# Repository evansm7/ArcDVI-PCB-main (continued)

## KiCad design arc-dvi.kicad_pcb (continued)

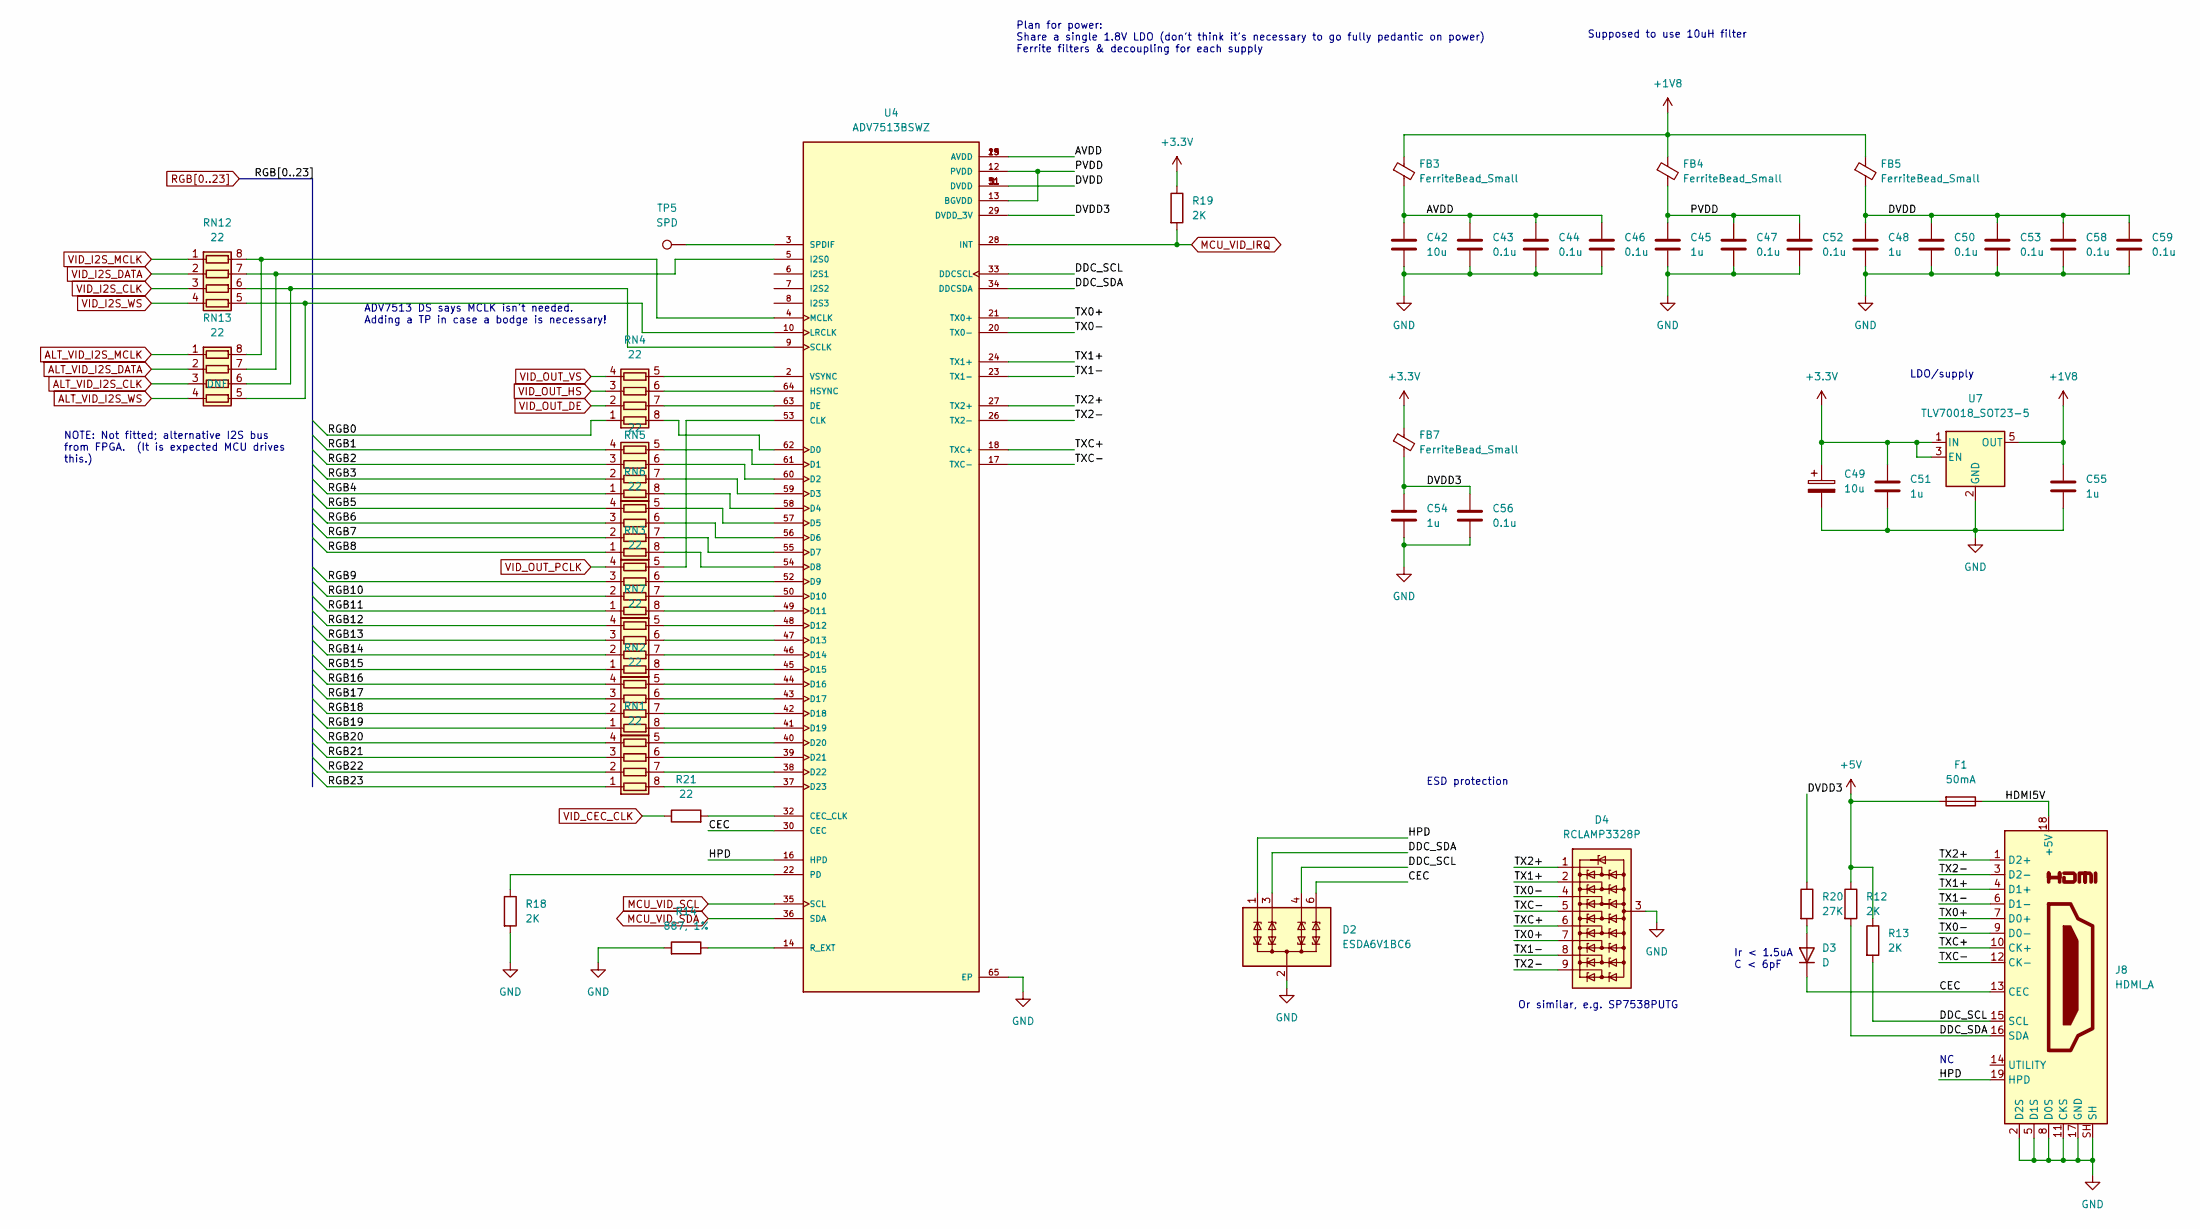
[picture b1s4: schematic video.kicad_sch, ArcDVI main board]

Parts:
C42: 10u; C_0603_1608Metric
C43, C44, C46, C47, C50, C52, C53, C56, C58, C59: 0.1u; C_0603_1608Metric
C45, C48, C51, C54, C55: 1u; C_0603_1608Metric
C49: 10u; CP_EIA-3528-21_Kemet-B
D2: ESDA6V1BC6; SOT-23-6
D3: D; D_0603_1608Metric
D4: RCLAMP3328P; UDFN-9_1.0x3.8mm_P0.5mm
F1: 50mA; Fuse_1206_3216Metric_Pad1.42x1.75mm_HandSolder
FB3, FB4, FB5, FB7: FerriteBead_Small; L_0603_1608Metric
J8: HDMI_A; HDMI_A_Molex_208658-1001_Horizontal
R12, R13, R18, R19: 2K; R_0603_1608Metric
R14: 887, 1%; R_0603_1608Metric
R20: 27K; R_0603_1608Metric
R21: 22; R_0603_1608Metric
RN1, RN2, RN3, RN4, RN5, RN6, RN7, RN12, RN13: 22; R_Array_Convex_4x0603
TP5: SPD; TestPoint_Pad_D1.0mm
U4: ADV7513BSWZ; QFP50P1200X1200X160-65N; PARTREV B
U7: TLV70018_SOT23-5; SOT-23-5

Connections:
+1V8: C55.1, FB3.1, FB4.1, FB5.1, U7.5 (OUT); also elsewhere on the board
+3V3: C49.1, C51.1, FB7.1, R19.1, U7.1 (IN), U7.3 (EN); also elsewhere on the board
+5V: F1.2, R12.1, R13.1; also elsewhere on the board
/Video/AVDD: C42.1, C43.1, C44.1, C46.1, FB3.2, U4.15 (AVDD), U4.19 (AVDD), U4.25 (AVDD)
/Video/CEC: D2.6 (TVS4), D3.1 (K), J8.13 (CEC), U4.30 (CEC)
/Video/DDC_SCL: D2.4 (TVS3), J8.15 (SCL), R13.2, U4.33 (DDCSCL)
/Video/DDC_SDA: D2.3 (TVS2), J8.16 (SDA), R12.2, U4.34 (DDCSDA)
/Video/DVDD: C48.1, C50.1, C53.1, C58.1, C59.1, FB5.2, U4.1 (DVDD), U4.11 (DVDD), U4.31 (DVDD), U4.51 (DVDD)
/Video/DVDD3: C54.1, C56.1, FB7.2, R20.1, U4.29 (DVDD_3V)
/Video/HDMI5V: F1.1, J8.18 (+5V)
/Video/HPD: D2.1 (TVS1), J8.19 (HPD), U4.16 (HPD)
/Video/PVDD: C45.1, C47.1, C52.1, FB4.2, U4.12 (PVDD), U4.13 (BGVDD)
/Video/TX0+: D4.7 (K6), J8.7 (D0+), U4.21 (TX0+)
/Video/TX0-: D4.4 (K3), J8.9 (D0-), U4.20 (TX0−)
/Video/TX1+: D4.2 (K2), J8.4 (D1+), U4.24 (TX1+)
/Video/TX1-: D4.8 (K7), J8.6 (D1-), U4.23 (TX1−)
/Video/TX2+: D4.1 (K1), J8.1 (D2+), U4.27 (TX2+)
/Video/TX2-: D4.9 (K8), J8.3 (D2-), U4.26 (TX2−)
/Video/TXC+: D4.6 (K5), J8.10 (CK+), U4.18 (TXC+)
/Video/TXC-: D4.5 (K4), J8.12 (CK-), U4.17 (TXC−)
ALT_VID_I2S_CLK: RN13.3 (R3.1); also elsewhere on the board
ALT_VID_I2S_DATA: RN13.2 (R2.1); also elsewhere on the board
ALT_VID_I2S_MCLK: RN13.1 (R1.1); also elsewhere on the board
ALT_VID_I2S_WS: RN13.4 (R4.1); also elsewhere on the board
GND: C42.2, C43.2, C44.2, C45.2, C46.2, C47.2, C48.2, C49.2, C50.2, C51.2, C52.2, C53.2, C54.2, C55.2, C56.2, C58.2, C59.2, D2.2 (COM), D2.5 (COM), D4.3 (A), J8.2 (D2S), J8.5 (D1S), J8.8 (D0S), J8.11 (CKS), J8.17 (GND), J8.SH, R14.2, R18.2, U4.65 (EP), U7.2 (GND); also elsewhere on the board
MCU_VID_IRQ: R19.2, U4.28 (INT); also elsewhere on the board
MCU_VID_SCL: U4.35 (SCL); also elsewhere on the board
MCU_VID_SDA: U4.36 (SDA); also elsewhere on the board
unnamed: D3.2 (A), R20.2
unnamed: R14.1, U4.14 (R_EXT)
unnamed: R18.1, U4.22 (PD)
unnamed: R21.2, U4.32 (CEC_CLK)
unnamed: RN1.5 (R4.2), U4.40 (D20)
unnamed: RN1.6 (R3.2), U4.39 (D21)
unnamed: RN1.7 (R2.2), U4.38 (D22)
unnamed: RN1.8 (R1.2), U4.37 (D23)
unnamed: RN2.5 (R4.2), U4.44 (D16)
unnamed: RN2.6 (R3.2), U4.43 (D17)
unnamed: RN2.7 (R2.2), U4.42 (D18)
unnamed: RN2.8 (R1.2), U4.41 (D19)
unnamed: RN3.5 (R4.2), U4.53 (CLK)
unnamed: RN3.6 (R3.2), U4.52 (D9)
unnamed: RN3.7 (R2.2), U4.50 (D10)
unnamed: RN3.8 (R1.2), U4.49 (D11)
unnamed: RN4.5 (R4.2), U4.2 (VSYNC)
unnamed: RN4.6 (R3.2), U4.64 (HSYNC)
unnamed: RN4.7 (R2.2), U4.63 (DE)
unnamed: RN4.8 (R1.2), U4.62 (D0)
unnamed: RN5.5 (R4.2), U4.61 (D1)
unnamed: RN5.6 (R3.2), U4.60 (D2)
unnamed: RN5.7 (R2.2), U4.59 (D3)
unnamed: RN5.8 (R1.2), U4.58 (D4)
unnamed: RN6.5 (R4.2), U4.57 (D5)
unnamed: RN6.6 (R3.2), U4.56 (D6)
unnamed: RN6.7 (R2.2), U4.55 (D7)
unnamed: RN6.8 (R1.2), U4.54 (D8)
unnamed: RN7.5 (R4.2), U4.48 (D12)
unnamed: RN7.6 (R3.2), U4.47 (D13)
unnamed: RN7.7 (R2.2), U4.46 (D14)
unnamed: RN7.8 (R1.2), U4.45 (D15)
unnamed: RN12.5 (R4.2), RN13.5 (R4.2), U4.10 (LRCLK)
unnamed: RN12.6 (R3.2), RN13.6 (R3.2), U4.9 (SCLK)
unnamed: RN12.7 (R2.2), RN13.7 (R2.2), U4.5 (I2S0)
unnamed: RN12.8 (R1.2), RN13.8 (R1.2), U4.4 (MCLK)
unnamed: TP5.1, U4.3 (SPDIF)
RGB0: RN4.1 (R1.1); also elsewhere on the board
RGB1: RN5.4 (R4.1); also elsewhere on the board
RGB2: RN5.3 (R3.1); also elsewhere on the board
RGB3: RN5.2 (R2.1); also elsewhere on the board
RGB4: RN5.1 (R1.1); also elsewhere on the board
RGB5: RN6.4 (R4.1); also elsewhere on the board
RGB6: RN6.3 (R3.1); also elsewhere on the board
RGB7: RN6.2 (R2.1); also elsewhere on the board
RGB8: RN6.1 (R1.1); also elsewhere on the board
RGB9: RN3.3 (R3.1); also elsewhere on the board
RGB10: RN3.2 (R2.1); also elsewhere on the board
RGB11: RN3.1 (R1.1); also elsewhere on the board
RGB12: RN7.4 (R4.1); also elsewhere on the board
RGB13: RN7.3 (R3.1); also elsewhere on the board
RGB14: RN7.2 (R2.1); also elsewhere on the board
RGB15: RN7.1 (R1.1); also elsewhere on the board
RGB16: RN2.4 (R4.1); also elsewhere on the board
RGB17: RN2.3 (R3.1); also elsewhere on the board
RGB18: RN2.2 (R2.1); also elsewhere on the board
RGB19: RN2.1 (R1.1); also elsewhere on the board
RGB20: RN1.4 (R4.1); also elsewhere on the board
RGB21: RN1.3 (R3.1); also elsewhere on the board
RGB22: RN1.2 (R2.1); also elsewhere on the board
RGB23: RN1.1 (R1.1); also elsewhere on the board
VID_CEC_CLK: R21.1; also elsewhere on the board
VID_I2S_CLK: RN12.3 (R3.1); also elsewhere on the board
VID_I2S_DATA: RN12.2 (R2.1); also elsewhere on the board
VID_I2S_MCLK: RN12.1 (R1.1); also elsewhere on the board
VID_I2S_WS: RN12.4 (R4.1); also elsewhere on the board
VID_OUT_DE: RN4.2 (R2.1); also elsewhere on the board
VID_OUT_HS: RN4.3 (R3.1); also elsewhere on the board
VID_OUT_PCLK: RN3.4 (R4.1); also elsewhere on the board
VID_OUT_VS: RN4.4 (R4.1); also elsewhere on the board

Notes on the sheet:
ADV7513 DS says MCLK isn't needed. Adding a TP in case a bodge is necessary!
Ir < 1.5uA C < 6pF
ESD protection
Supposed to use 10uH filter
Plan for power: Share a single 1.8V LDO (don't think it's necessary to go fully pedantic on power) Ferrite filters & decoupling for each supply
Or similar, e.g. SP7538PUTG
LDO/supply
NOTE: Not fitted; alternative I2S bus from FPGA. (It is expected MCU drives this.)

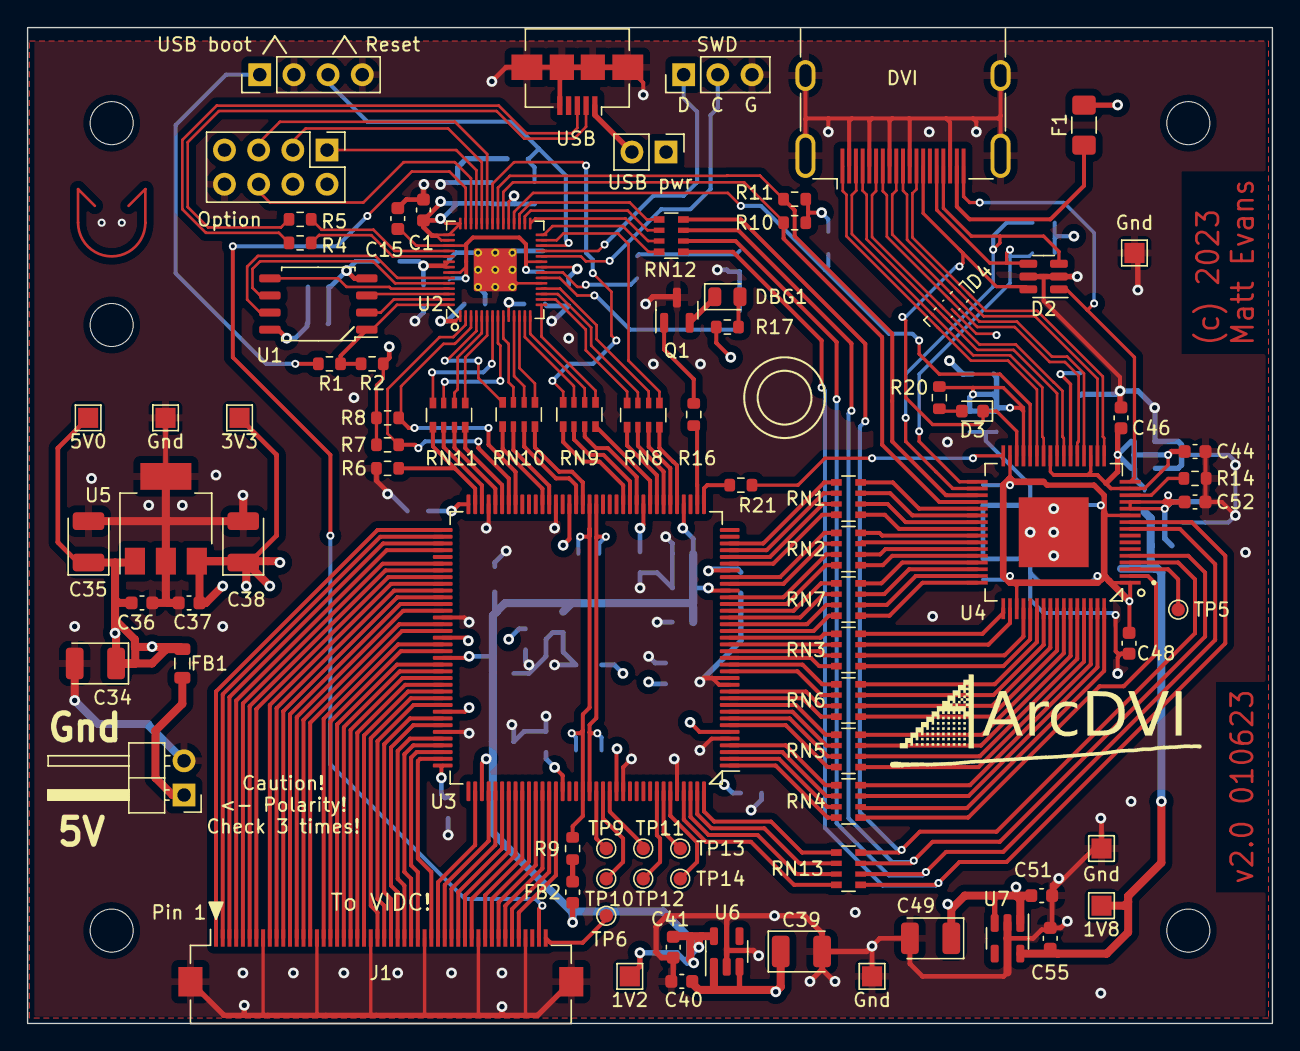
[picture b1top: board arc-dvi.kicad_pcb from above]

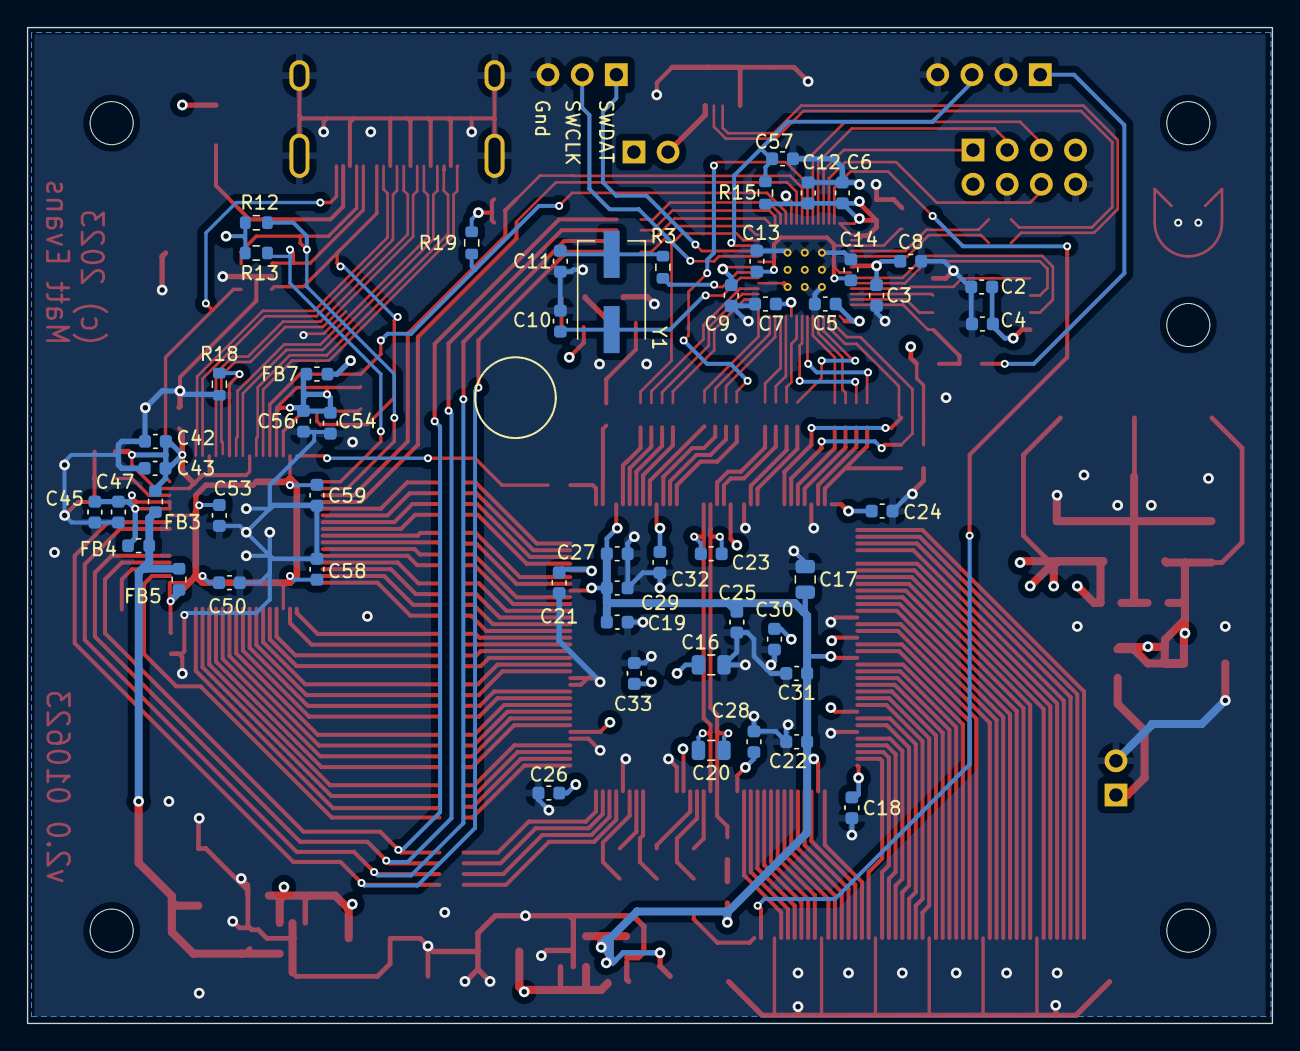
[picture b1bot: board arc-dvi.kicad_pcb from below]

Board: 4 copper layers, 92.5 x 74.0 mm, 142 parts (53 on the bottom side), 213 nets.

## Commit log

2022-06-20 v1.0 board
2022-07-07 Oops, no, _this_ is v1.0
    ;-)
2023-05-19 v2: ADV7513 and FFC
    Large work much progress - almost routed
2023-05-21 2.0 candiate: routed, looks neat, passes DRC
    DVI differential pairs aren't tuned that nicely, but 'probs ok'
2023-05-22 Tuned pairs (better, at least)
2023-05-22 Tweaked layout, marked plcc centre
2023-05-22 Moved Gnd TP, added decoration
2023-05-22 Updated date, made board narrower, added dims
2023-06-01 Made board slightly smaller, re-centered contact point, tidied
    Good to go, DRC clean.
2023-06-11 Add README, licence
